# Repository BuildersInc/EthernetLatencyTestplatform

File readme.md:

# Ethernet Latency Testplatform

Used to measure the time difference
within the Ethernet communication between
two uC's

Created for my Bachelor Thesis

## External Components

- [ESP32 WROOM32](https://www.amazon.de/dp/B0D8635YZ6)
- [LAN8720 Board](https://www.amazon.de/TECNOIOT-Ethernet-Transceiver-Interface-Development/dp/B07VN9Q4QK)

## ESP 32 Pinout

| GPIO | Function               |
|------|----------              |
|00    |RETCLK                  |
|12    |Output detection        |
|13    |Input detection         |
|14    |Master & Slave          |
|17    |NC		        		|
|18    |MDC                     |
|19    |TX 0                    |
|21    |TX Enable               |
|22    |TX 1                    |
|23    |MDIO                    |
|25    |RX 0                    |
|26    |RX  1                   |
|27    |CRS                     |

## Necessary Modifications

- Remove ClockGen from LAN8720 Board and use ESP32 as source

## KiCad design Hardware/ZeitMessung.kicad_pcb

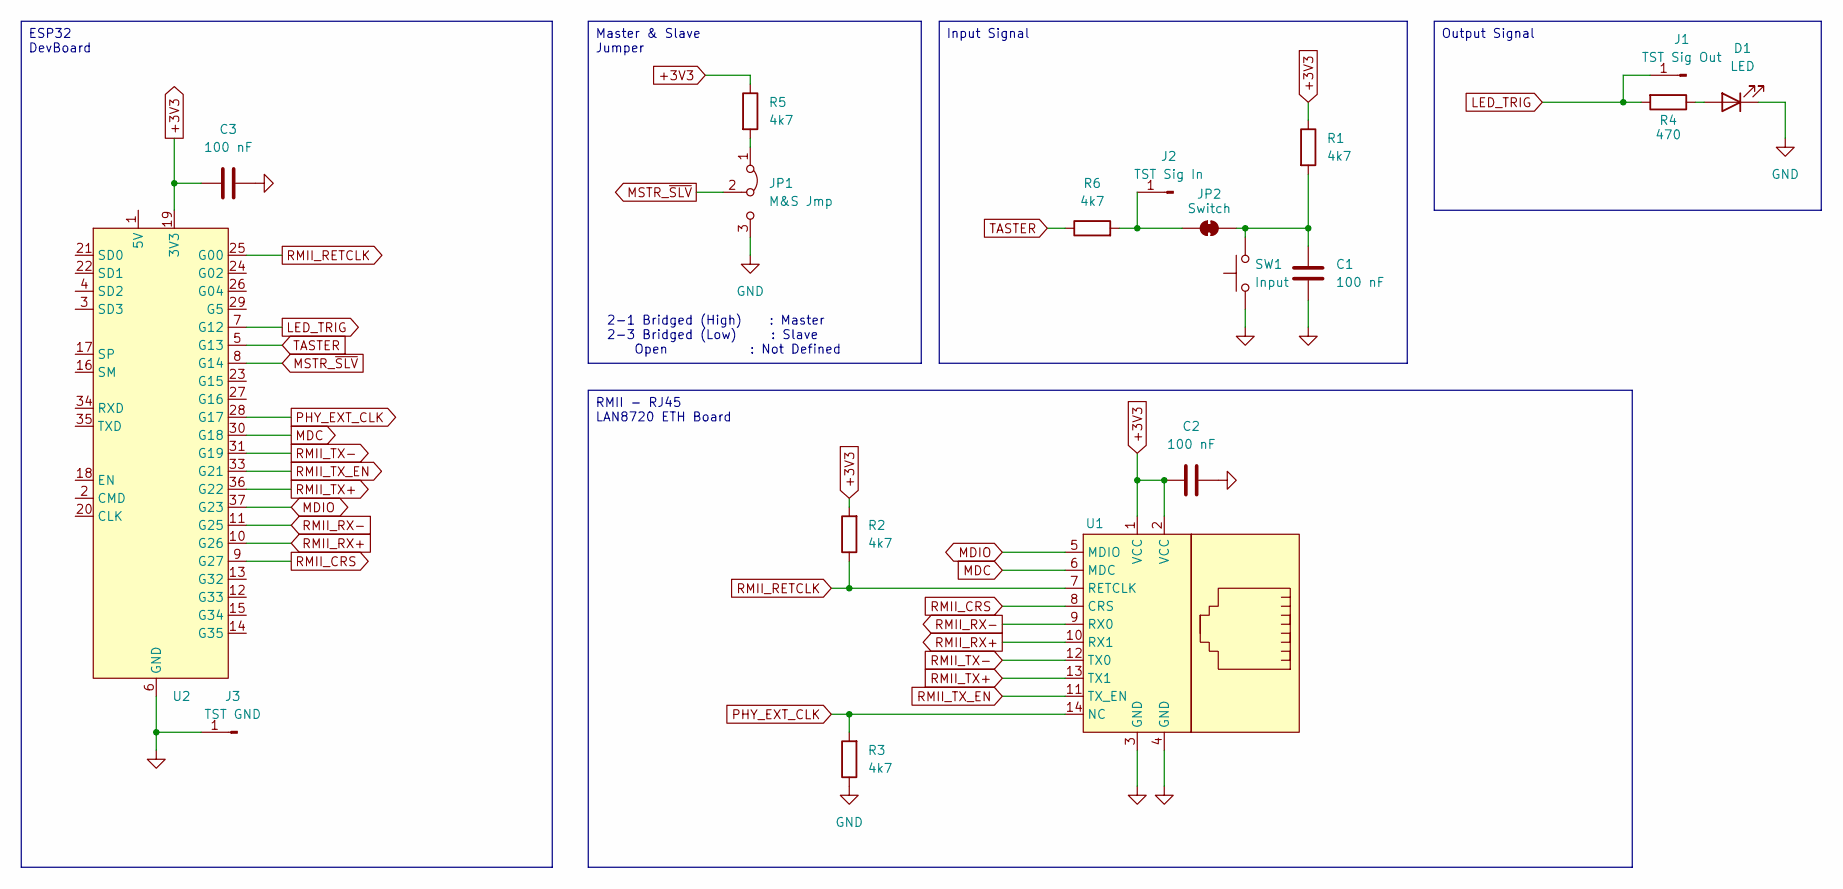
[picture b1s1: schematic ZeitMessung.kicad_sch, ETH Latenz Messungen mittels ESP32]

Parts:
C1, C2, C3: 100 nF; C_0603_1608Metric
D1: LED; LED_D5.0mm
J1: TST Sig Out; PinHeader_1x01_P2.54mm_Vertical
J2: TST Sig In; PinHeader_1x01_P2.54mm_Vertical
J3: TST GND; PinHeader_1x01_P2.54mm_Vertical
JP1: M&S Jmp; PinHeader_1x03_P2.54mm_Vertical
JP2: Switch; SolderJumper-2_P1.3mm_Open_RoundedPad1.0x1.5mm
R1, R2, R3, R5, R6: 4k7; R_0603_1608Metric
R4: 470; R_0603_1608Metric
SW1: Input; SW_PUSH_6mm
U1: LAN8720 DevBoard
U2: ESP32-WROOM

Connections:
+3V3: C2.1, C3.1, R1.1, R2.2, R5.1, U1.1 (VCC), U1.2 (VCC), U2.19 (3V3)
GND: C1.1, C2.2, C3.2, D1.1 (K), J3.1, JP1.3 (B), R3.1, SW1.1, U1.3 (GND), U1.4 (GND), U2.6 (GND)
LED_TRIG: J1.1, R4.2, U2.7 (G12)
MDC: U1.6 (MDC), U2.30 (G18)
MDIO: U1.5 (MDIO), U2.37 (G23)
MSTR_~SLV: JP1.2 (C), U2.8 (G14)
unnamed: D1.2 (A), R4.1
unnamed: J2.1, JP2.1 (A), R6.2
unnamed: JP1.1 (A), R5.2
unnamed: C1.2, JP2.2 (B), R1.2, SW1.2
PHY_EXT_CLK: R3.2, U1.14 (NC), U2.28 (G17)
RMII_CRS: U1.8 (CRS), U2.9 (G27)
RMII_RETCLK: R2.1, U1.7 (RETCLK), U2.25 (G00)
RMII_RX+: U1.10 (RX1), U2.10 (G26)
RMII_RX-: U1.9 (RX0), U2.11 (G25)
RMII_TX+: U1.13 (TX1), U2.36 (G22)
RMII_TX-: U1.12 (TX0), U2.31 (G19)
RMII_TX_EN: U1.11 (TX_EN), U2.33 (G21)
TASTER: R6.1, U2.5 (G13)

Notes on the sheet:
2-1 Bridged (High) : Master 2-3 Bridged (Low) : Slave Open : Not Defined
ESP32 DevBoard
Output Signal
RMII - RJ45 LAN8720 ETH Board
Input Signal
Master & Slave Jumper

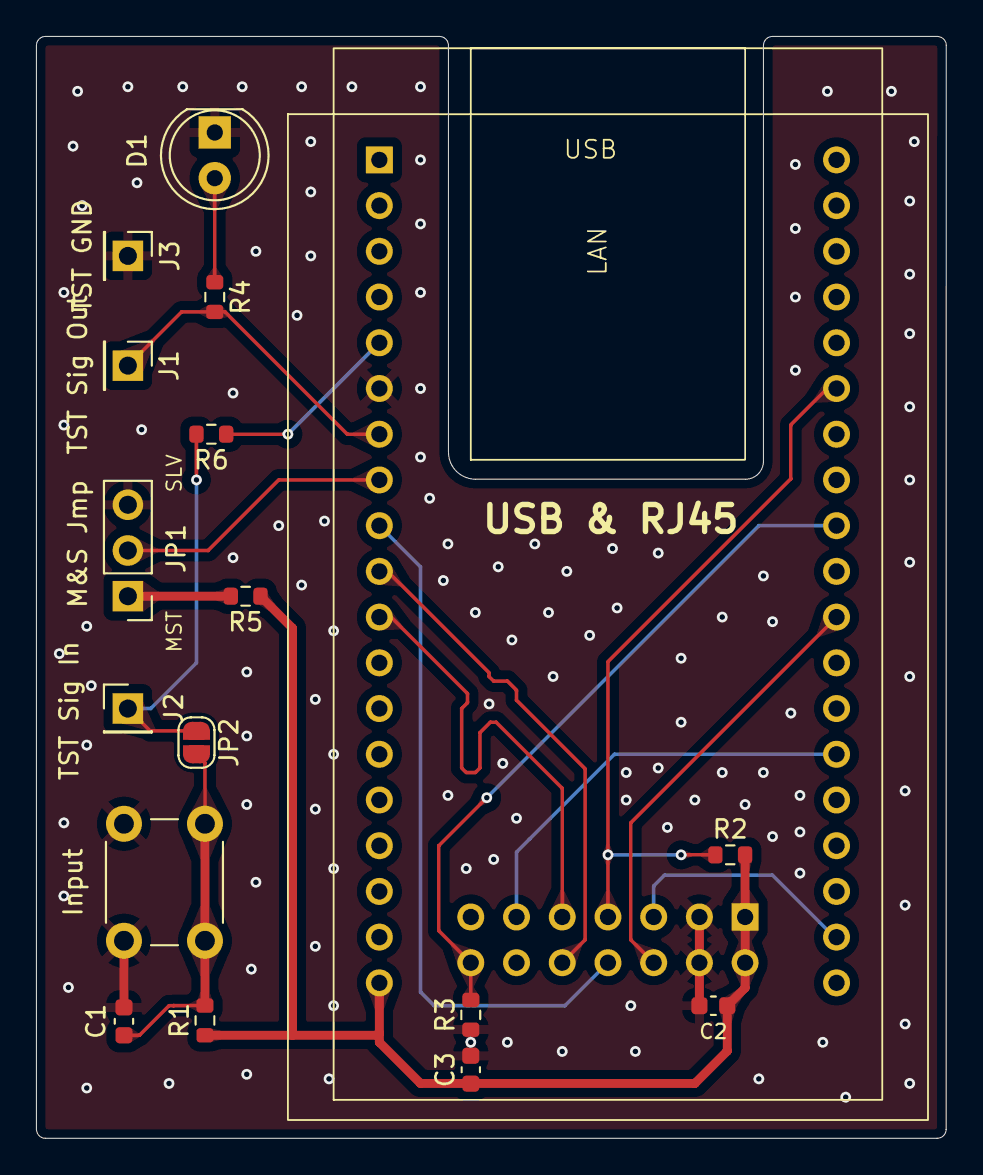
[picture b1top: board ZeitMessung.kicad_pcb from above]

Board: 4 copper layers, 50.5 x 61.2 mm, 18 parts (0 on the bottom side), 19 nets.

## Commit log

2025-05-21 Combine Two temporary repos into one
2025-05-21 Add info into readme
2025-05-21 Create LICENSE
2025-10-23 Some Pictures
